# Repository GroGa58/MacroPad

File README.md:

# Raspberry Pi Pico Macropad

## Project Description
This project is a **Raspberry Pi Pico-based**, portable, and customizable **macropad** design.  
It features **9 buttons**, **1 potentiometer**, and **1 display**. The display is used to visually monitor the status of buttons or the potentiometer.

---

## Features
- 9 programmable buttons  
- 1 analog potentiometer  
- 1 display (OLED/LCD, depending on the project requirements)  
- Works with Raspberry Pi Pico  
- Hardware-focused design, easily integrable into other projects  

---

## Hardware
- Raspberry Pi Pico  
- 9x Push Buttons  
- 1x Potentiometer  
- 1x OLED/LCD Display  
- Connecting wires and resistors (optional)  
- PCB or breadboard design  

---

## License
This project is open-source under the **MIT License**.  
You are free to use, modify, and share it.

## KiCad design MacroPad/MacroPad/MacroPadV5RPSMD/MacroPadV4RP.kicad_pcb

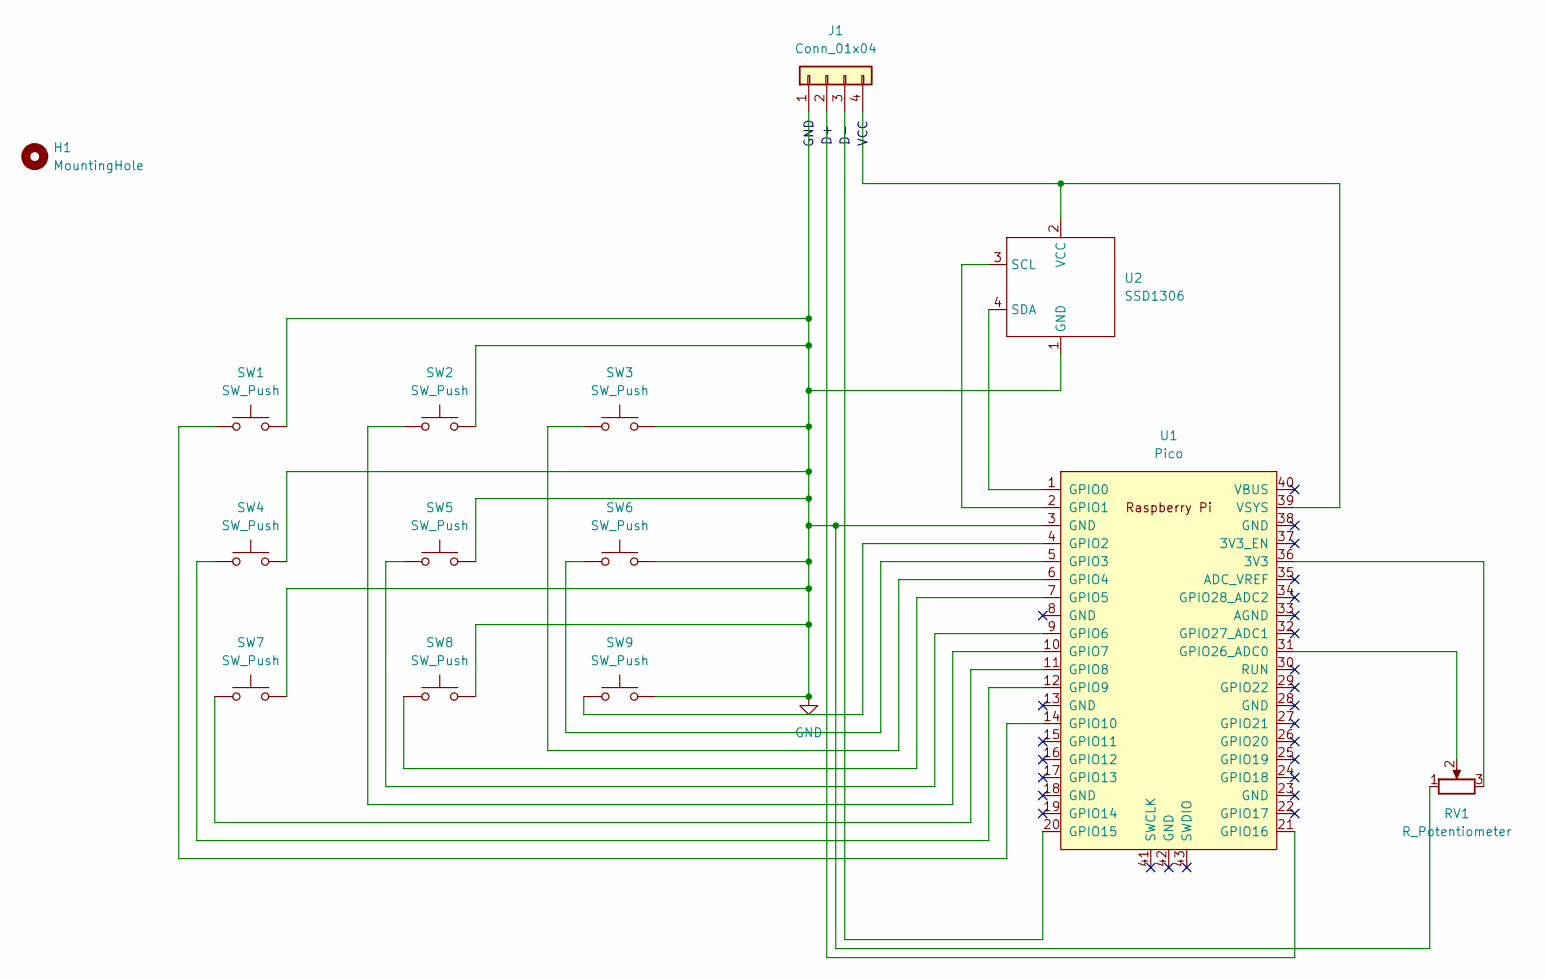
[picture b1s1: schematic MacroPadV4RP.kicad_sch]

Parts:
H1: MountingHole; MountingHole_2.5mm
J1: Conn_01x04; SolderWire-0.25sqmm_1x04_P4.2mm_D0.65mm_OD1.7mm
RV1: R_Potentiometer; Potentiometer_Alps_RK163_Single_Horizontal
SW1, SW2, SW3, SW4, SW5, SW6, SW7, SW8, SW9: SW_Push; SW_Cherry_MX_1.00u_Plate
U1: Pico; RPi_Pico_SMD_TH
U2: SSD1306

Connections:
GND: J1.1, RV1.1, SW1.2, SW2.2, SW3.2, SW4.2, SW5.2, SW6.2, SW7.2, SW8.2, SW9.2, U1.3 (GND), U2.1 (GND)
unnamed: J1.2, U1.21 (GPIO16)
unnamed: J1.3, U1.20 (GPIO15)
unnamed: J1.4, U1.39 (VSYS), U2.2 (VCC)
unnamed: RV1.3, U1.36 (3V3)
unnamed: U1.1 (GPIO0), U2.4 (SDA)
unnamed: U1.2 (GPIO1), U2.3 (SCL)
unnamed: SW9.1, U1.4 (GPIO2)
unnamed: SW6.1, U1.5 (GPIO3)
unnamed: SW3.1, U1.6 (GPIO4)
unnamed: SW8.1, U1.7 (GPIO5)
unnamed: SW5.1, U1.9 (GPIO6)
unnamed: SW2.1, U1.10 (GPIO7)
unnamed: SW7.1, U1.11 (GPIO8)
unnamed: SW4.1, U1.12 (GPIO9)
unnamed: SW1.1, U1.14 (GPIO10)
unnamed: RV1.2, U1.31 (GPIO26_ADC0)

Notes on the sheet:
GND
VCC

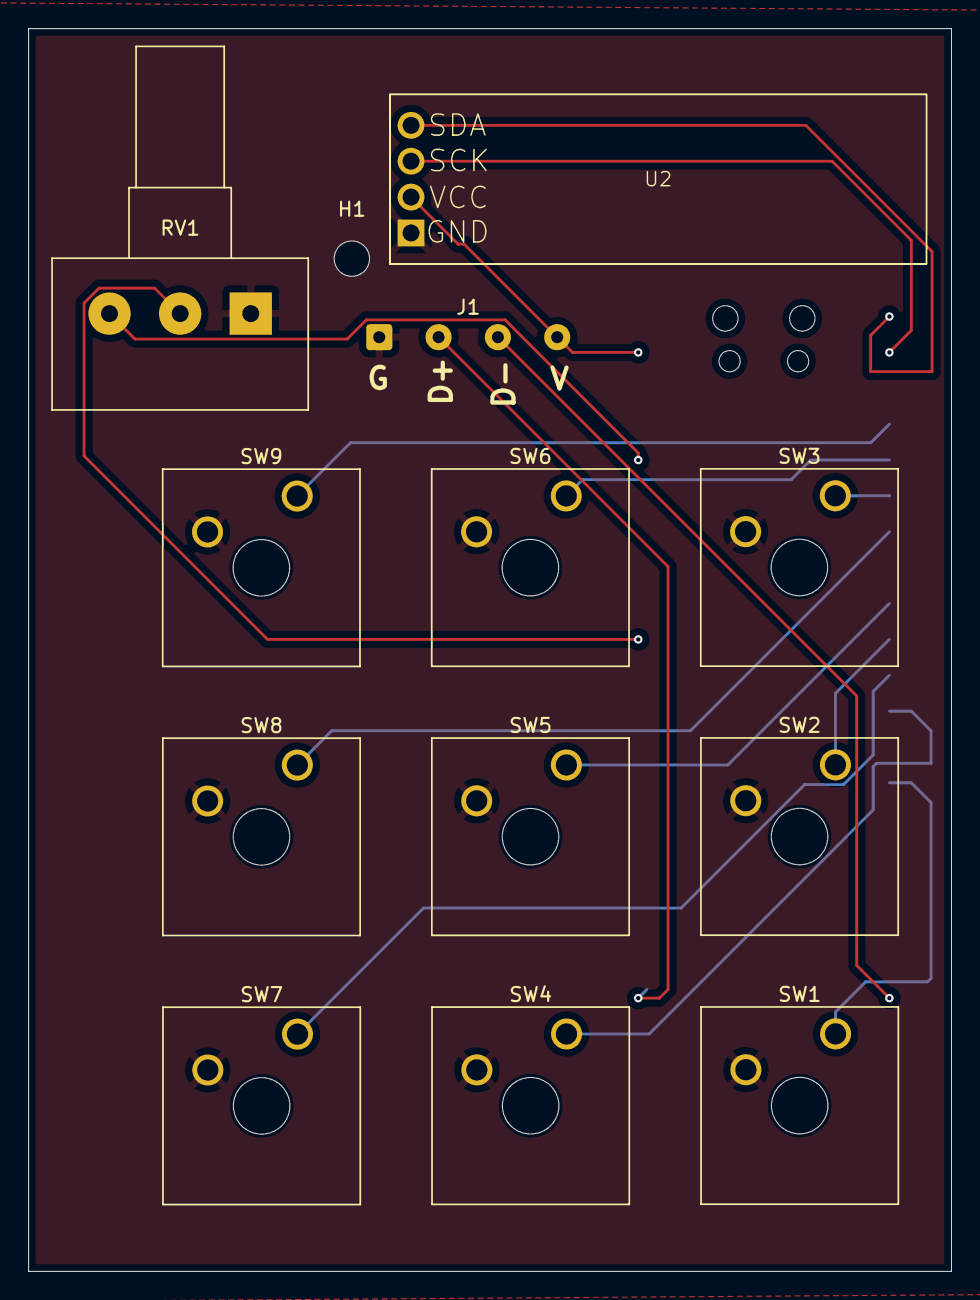
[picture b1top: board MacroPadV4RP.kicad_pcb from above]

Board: 2 copper layers, 65.4 x 88.0 mm, 14 parts (1 on the bottom side), 17 nets.

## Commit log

2025-10-17 README.md
